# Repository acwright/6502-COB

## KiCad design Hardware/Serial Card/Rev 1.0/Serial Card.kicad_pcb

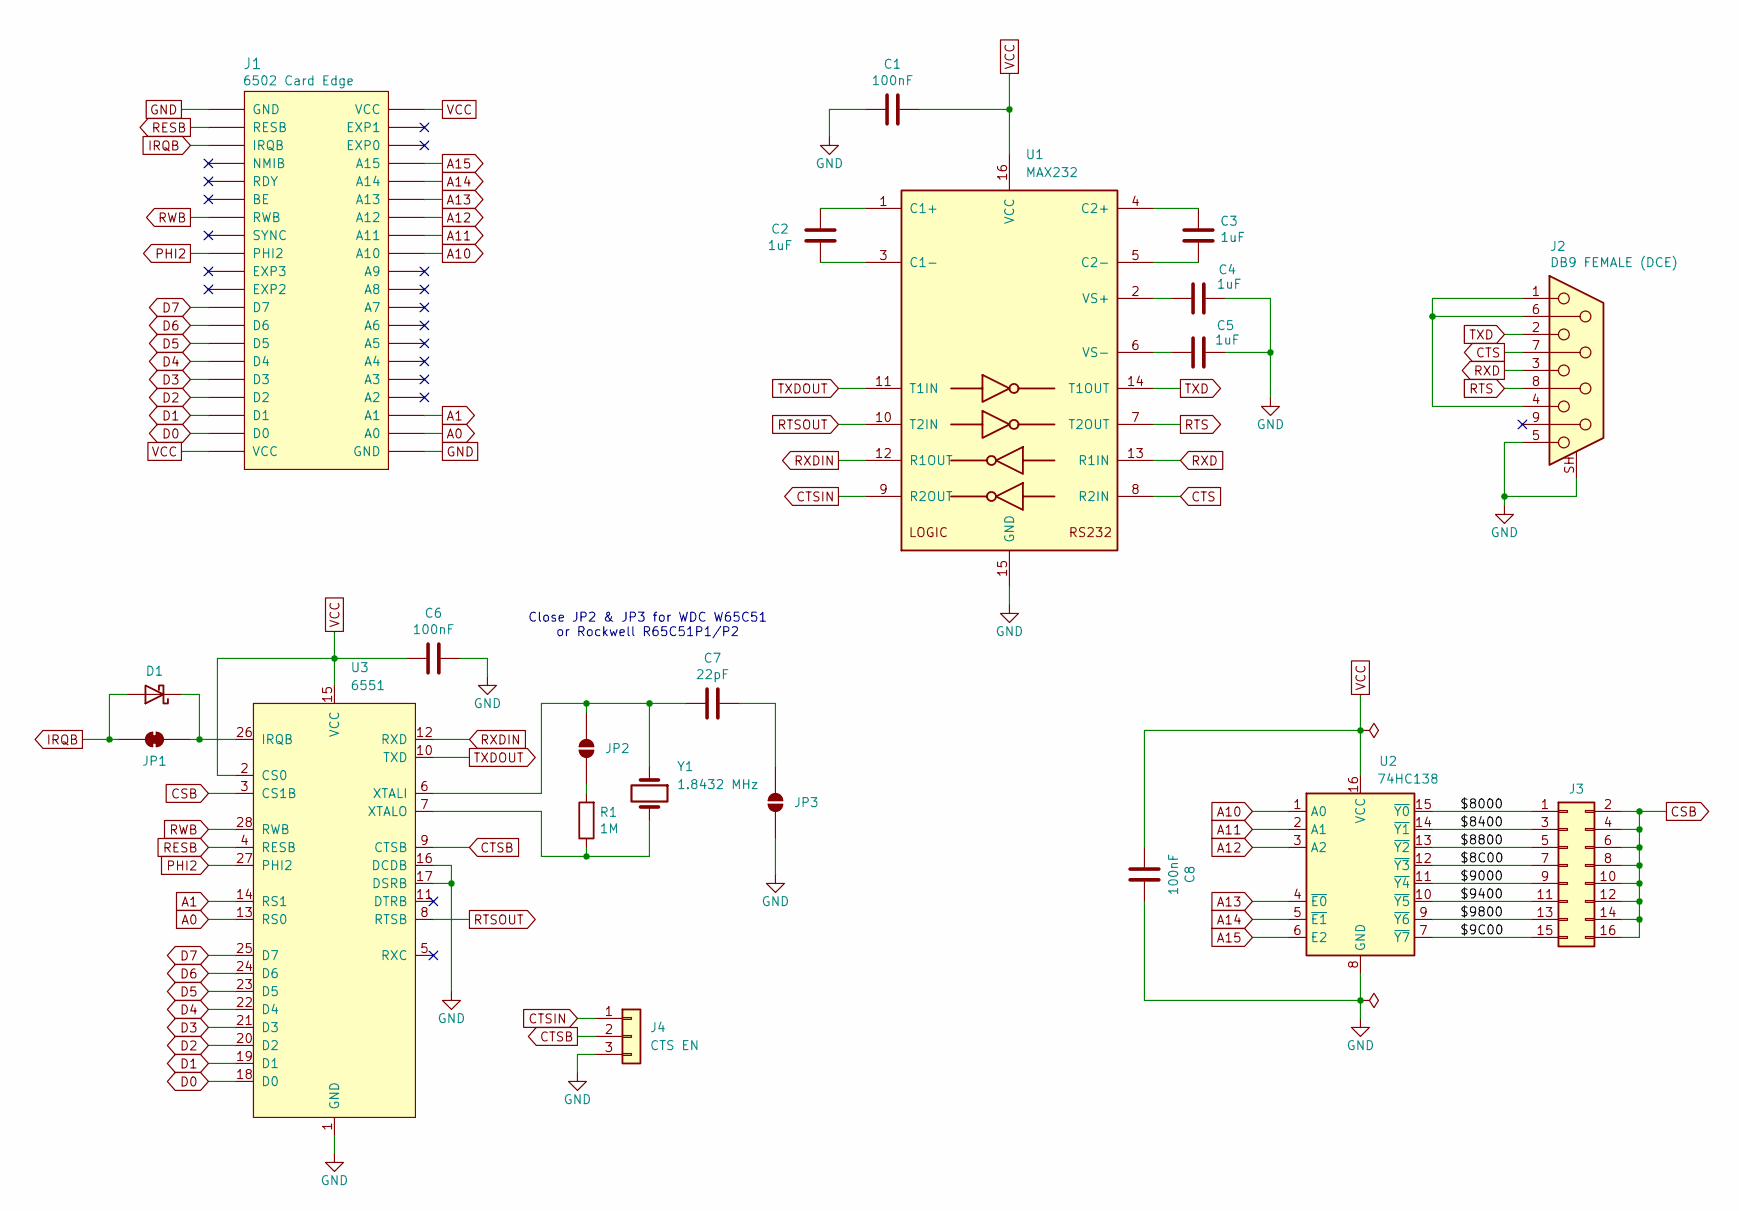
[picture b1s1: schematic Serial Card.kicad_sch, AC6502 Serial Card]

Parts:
C1, C6, C8: 100nF; C_0805_2012Metric; LCSC C49678
C2, C3, C4, C5: 1uF; C_0805_2012Metric; LCSC C28323
C7: 22pF; C_0805_2012Metric; LCSC C1804
D1: BAT85; D_DO-35_SOD27_P7.62mm_Horizontal; Digikey BAT85SCT-ND
J1: 6502 Card Edge
J2: DB9 FEMALE (DCE); DSUB-9_Socket_Horizontal_P2.77x2.84mm_EdgePinOffset7.70mm_H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; Digikey 609-1487-ND
J3: Conn_02x08_Odd_Even; PinHeader_2x08_P2.54mm_Vertical; Digikey S2011EC-40-ND
J4: CTS EN; PinHeader_1x03_P2.54mm_Vertical; Digikey S1011EC-40-ND
JP1: SolderJumper_2_Bridged; SolderJumper-2_P1.3mm_Bridged_RoundedPad1.0x1.5mm
JP2, JP3: SolderJumper_2_Open; SolderJumper-2_P1.3mm_Open_RoundedPad1.0x1.5mm
R1: 1M; R_0805_2012Metric; LCSC C17514
U1: MAX232; SOIC-16; LCSC C59824
U2: 74HC138; SOIC-16_3.9x9.9mm_P1.27mm; LCSC C5602
U3: 6551; DIP-28_W15.24mm_Socket_LongPads
Y1: 1.8432 MHz; Crystal_HC49-U_Vertical; Digikey 535-9009-ND

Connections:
/$8C00: J3.7, U2.12 (~Y3)
/$9C00: J3.15, U2.7 (~Y7)
/$8000: J3.1, U2.15 (~Y0)
/$8400: J3.3, U2.14 (~Y1)
/$8800: J3.5, U2.13 (~Y2)
/$9000: J3.9, U2.11 (~Y4)
/$9400: J3.11, U2.10 (~Y5)
/$9800: J3.13, U2.9 (~Y6)
A0: J1.A0, U3.13 (RS0)
A1: J1.A1, U3.14 (RS1)
A10: J1.A10, U2.1 (A0)
A11: J1.A11, U2.2 (A1)
A12: J1.A12, U2.3 (A2)
A13: J1.A13, U2.4 (~E0)
A14: J1.A14, U2.5 (~E1)
A15: J1.A15, U2.6 (E2)
CSB: J3.2, J3.4, J3.6, J3.8, J3.10, J3.12, J3.14, J3.16, U3.3 (CS1B)
CTS: J2.7, U1.8 (R2IN)
CTSB: J4.2, U3.9 (CTSB)
CTSIN: J4.1, U1.9 (R2OUT)
D0: J1.D0, U3.18 (D0)
D1: J1.D1, U3.19 (D1)
D2: J1.D2, U3.20 (D2)
D3: J1.D3, U3.21 (D3)
D4: J1.D4, U3.22 (D4)
D5: J1.D5, U3.23 (D5)
D6: J1.D6, U3.24 (D6)
D7: J1.D7, U3.25 (D7)
GND: C1.1, C4.2, C5.2, C6.2, C8.2, J1.GND, J2.5, J2.SH (PAD), J4.3, JP3.1 (A), U1.15 (GND), U2.8 (GND), U3.1 (GND), U3.16 (DCDB), U3.17 (DSRB)
IRQB: D1.2 (A), J1.IRQB, JP1.1 (A)
unnamed: D1.1 (K), JP1.2 (B), U3.26 (IRQB)
unnamed: J2.1, J2.4, J2.6
unnamed: JP2.1 (A), R1.2
unnamed: C7.2, JP2.2 (B), U3.6 (XTALI), Y1.1
unnamed: C7.1, JP3.2 (B)
unnamed: C2.1, U1.1 (C1+)
unnamed: C2.2, U1.3 (C1-)
unnamed: C3.1, U1.4 (C2+)
unnamed: C3.2, U1.5 (C2-)
unnamed: C4.1, U1.2 (VS+)
unnamed: C5.1, U1.6 (VS-)
unnamed: R1.1, U3.7 (XTALO), Y1.2
PHI2: J1.PHI2, U3.27 (PHI2)
RESB: J1.RESB, U3.4 (RESB)
RTS: J2.8, U1.7 (T2OUT)
RTSOUT: U1.10 (T2IN), U3.8 (RTSB)
RWB: J1.RWB, U3.28 (RWB)
RXD: J2.3, U1.13 (R1IN)
RXDIN: U1.12 (R1OUT), U3.12 (RXD)
TXD: J2.2, U1.14 (T1OUT)
TXDOUT: U1.11 (T1IN), U3.10 (TXD)
VCC: C1.2, C6.1, C8.1, J1.VCC, U1.16 (VCC), U2.16 (VCC), U3.2 (CS0), U3.15 (VCC)

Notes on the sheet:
Close JP2 & JP3 for WDC W65C51 or Rockwell R65C51P1/P2

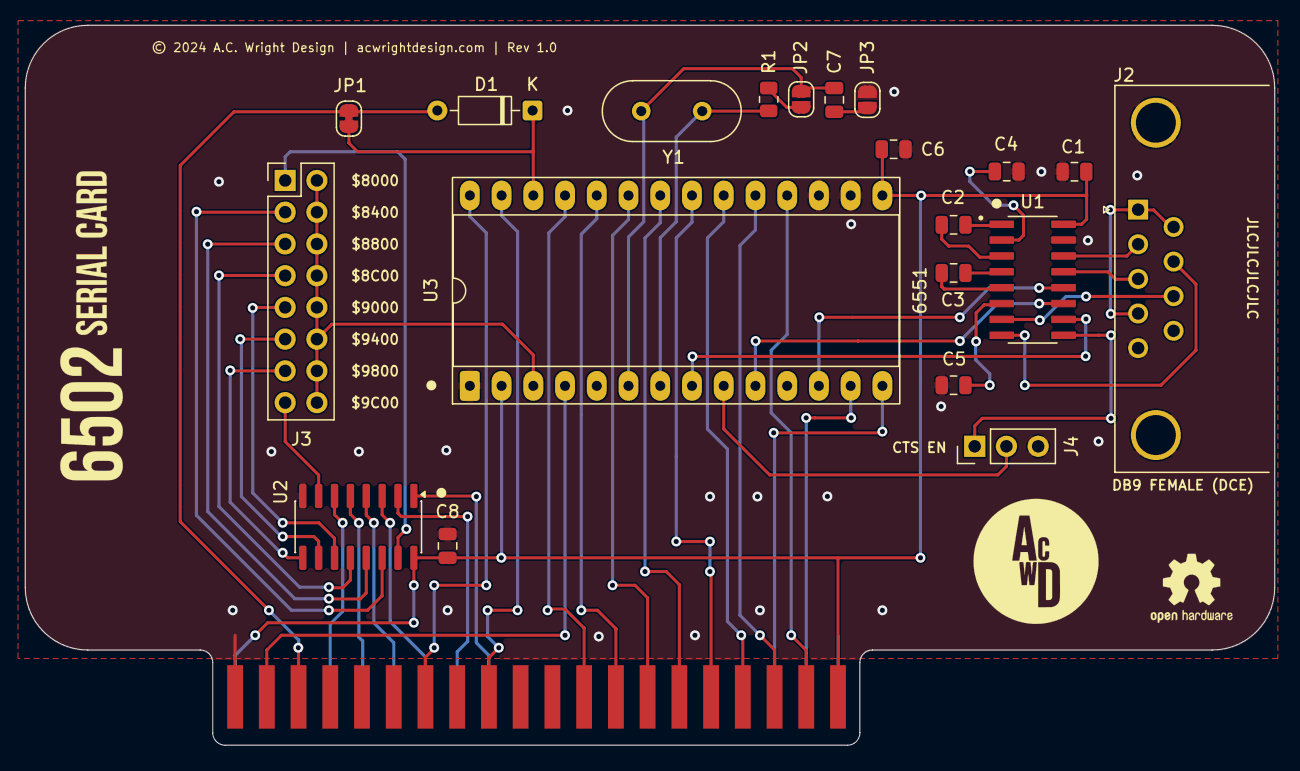
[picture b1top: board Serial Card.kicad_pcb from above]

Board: 2 copper layers, 100.0 x 57.6 mm, 21 parts (0 on the bottom side), 52 nets.

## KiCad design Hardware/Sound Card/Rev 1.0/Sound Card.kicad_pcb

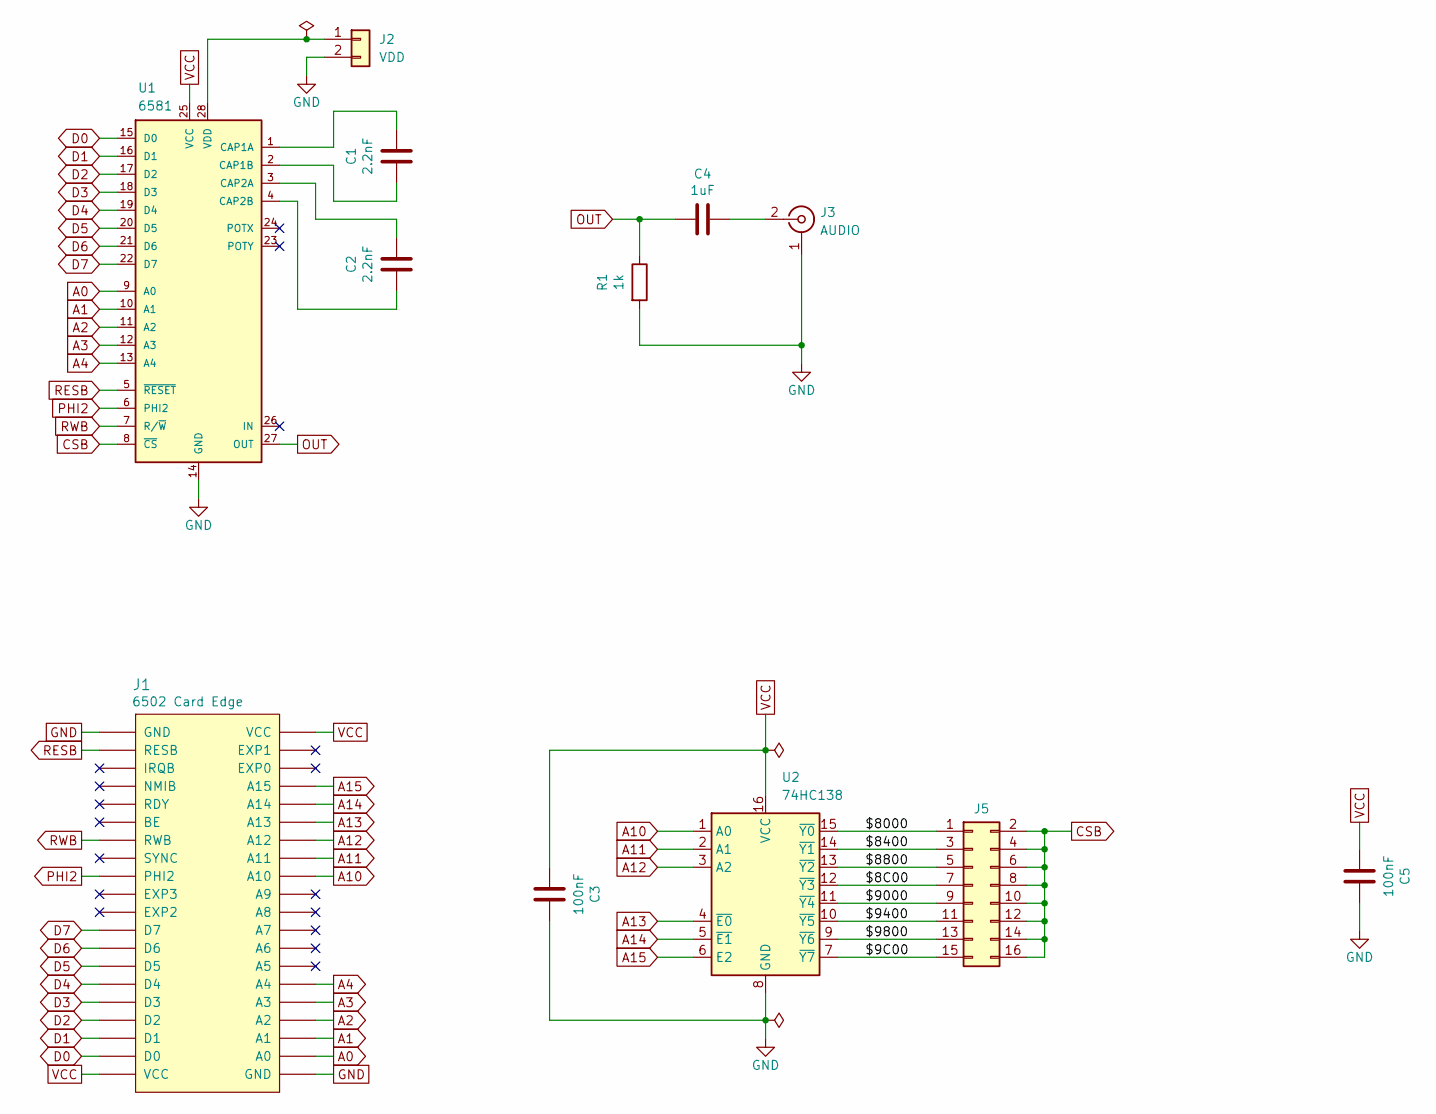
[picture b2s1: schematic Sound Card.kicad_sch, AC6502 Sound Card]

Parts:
C1, C2: 2.2nF; C_0805_2012Metric; LCSC C28260
C3, C5: 100nF; C_0805_2012Metric; LCSC C49678
C4: 1uF; C_0805_2012Metric; LCSC C28323
J1: 6502 Card Edge
J2: VDD; JST_XH_B2B-XH-A_1x02_P2.50mm_Vertical; Digikey 455-B2B-XH-A-ND
J3: AUDIO; RCA Jack White; Digikey PJRAN1X1U02X-ND
J5: Conn_02x08_Odd_Even; PinHeader_2x08_P2.54mm_Vertical; Digikey S2011EC-40-ND
R1: 1k; R_0805_2012Metric; LCSC C17513
U1: 6581; DIP-28_W15.24mm_Socket_LongPads
U2: 74HC138; SOIC-16_3.9x9.9mm_P1.27mm; LCSC C5602

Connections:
/$8C00: J5.7, U2.12 (~Y3)
/$9C00: J5.15, U2.7 (~Y7)
/$8000: J5.1, U2.15 (~Y0)
/$8400: J5.3, U2.14 (~Y1)
/$8800: J5.5, U2.13 (~Y2)
/$9000: J5.9, U2.11 (~Y4)
/$9400: J5.11, U2.10 (~Y5)
/$9800: J5.13, U2.9 (~Y6)
A0: J1.A0, U1.9 (A0)
A1: J1.A1, U1.10 (A1)
A2: J1.A2, U1.11 (A2)
A3: J1.A3, U1.12 (A3)
A4: J1.A4, U1.13 (A4)
A10: J1.A10, U2.1 (A0)
A11: J1.A11, U2.2 (A1)
A12: J1.A12, U2.3 (A2)
A13: J1.A13, U2.4 (~E0)
A14: J1.A14, U2.5 (~E1)
A15: J1.A15, U2.6 (E2)
CSB: J5.2, J5.4, J5.6, J5.8, J5.10, J5.12, J5.14, J5.16, U1.8 (~CS)
D0: J1.D0, U1.15 (D0)
D1: J1.D1, U1.16 (D1)
D2: J1.D2, U1.17 (D2)
D3: J1.D3, U1.18 (D3)
D4: J1.D4, U1.19 (D4)
D5: J1.D5, U1.20 (D5)
D6: J1.D6, U1.21 (D6)
D7: J1.D7, U1.22 (D7)
GND: C3.2, C5.2, J1.GND, J2.2, J3.1 (Ext), R1.2, U1.14 (GND), U2.8 (GND)
unnamed: J2.1, U1.28 (VDD)
unnamed: C4.2, J3.2 (In)
unnamed: C1.2, U1.1 (CAP1A)
unnamed: C1.1, U1.2 (CAP1B)
unnamed: C2.2, U1.3 (CAP2A)
unnamed: C2.1, U1.4 (CAP2B)
OUT: C4.1, R1.1, U1.27 (OUT)
PHI2: J1.PHI2, U1.6 (PHI2)
RESB: J1.RESB, U1.5 (~RESET)
RWB: J1.RWB, U1.7 (R/~W)
VCC: C3.1, C5.1, J1.VCC, U1.25 (VCC), U2.16 (VCC)

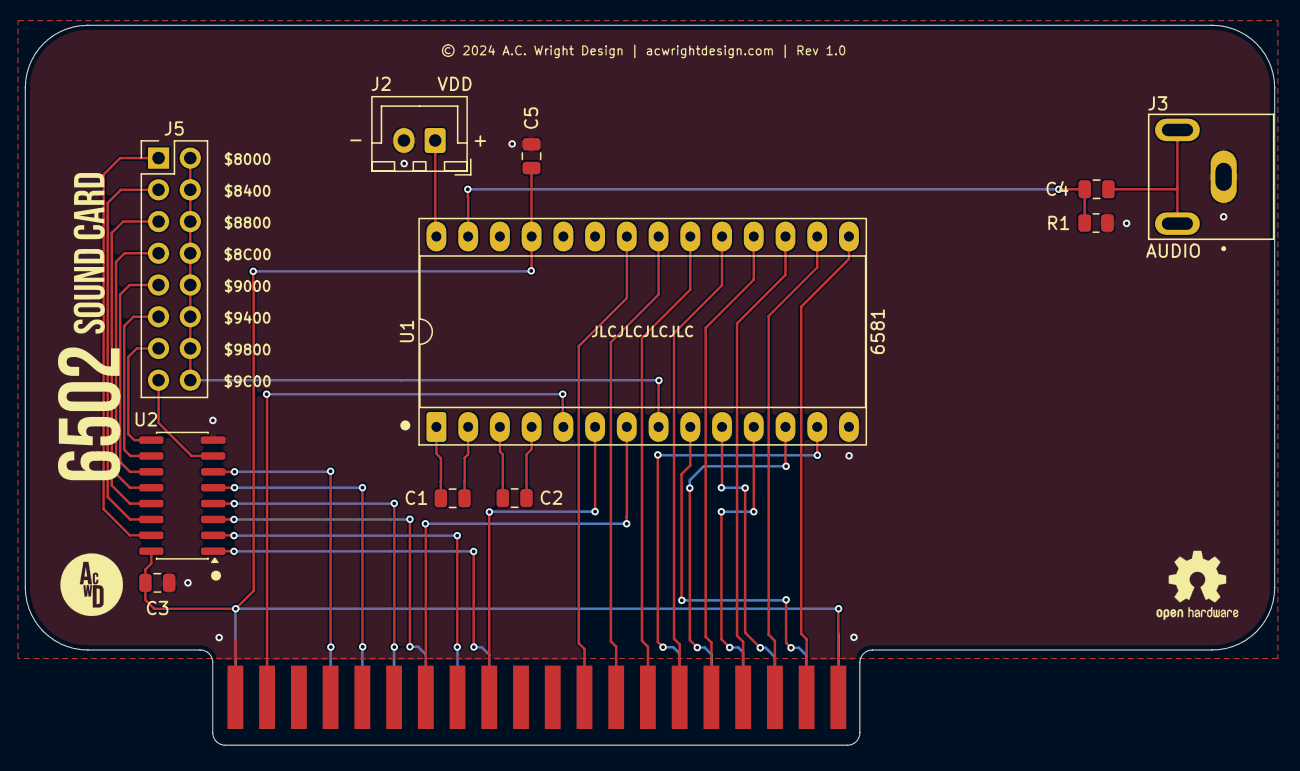
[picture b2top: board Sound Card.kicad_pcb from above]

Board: 2 copper layers, 100.0 x 57.6 mm, 12 parts (0 on the bottom side), 40 nets.

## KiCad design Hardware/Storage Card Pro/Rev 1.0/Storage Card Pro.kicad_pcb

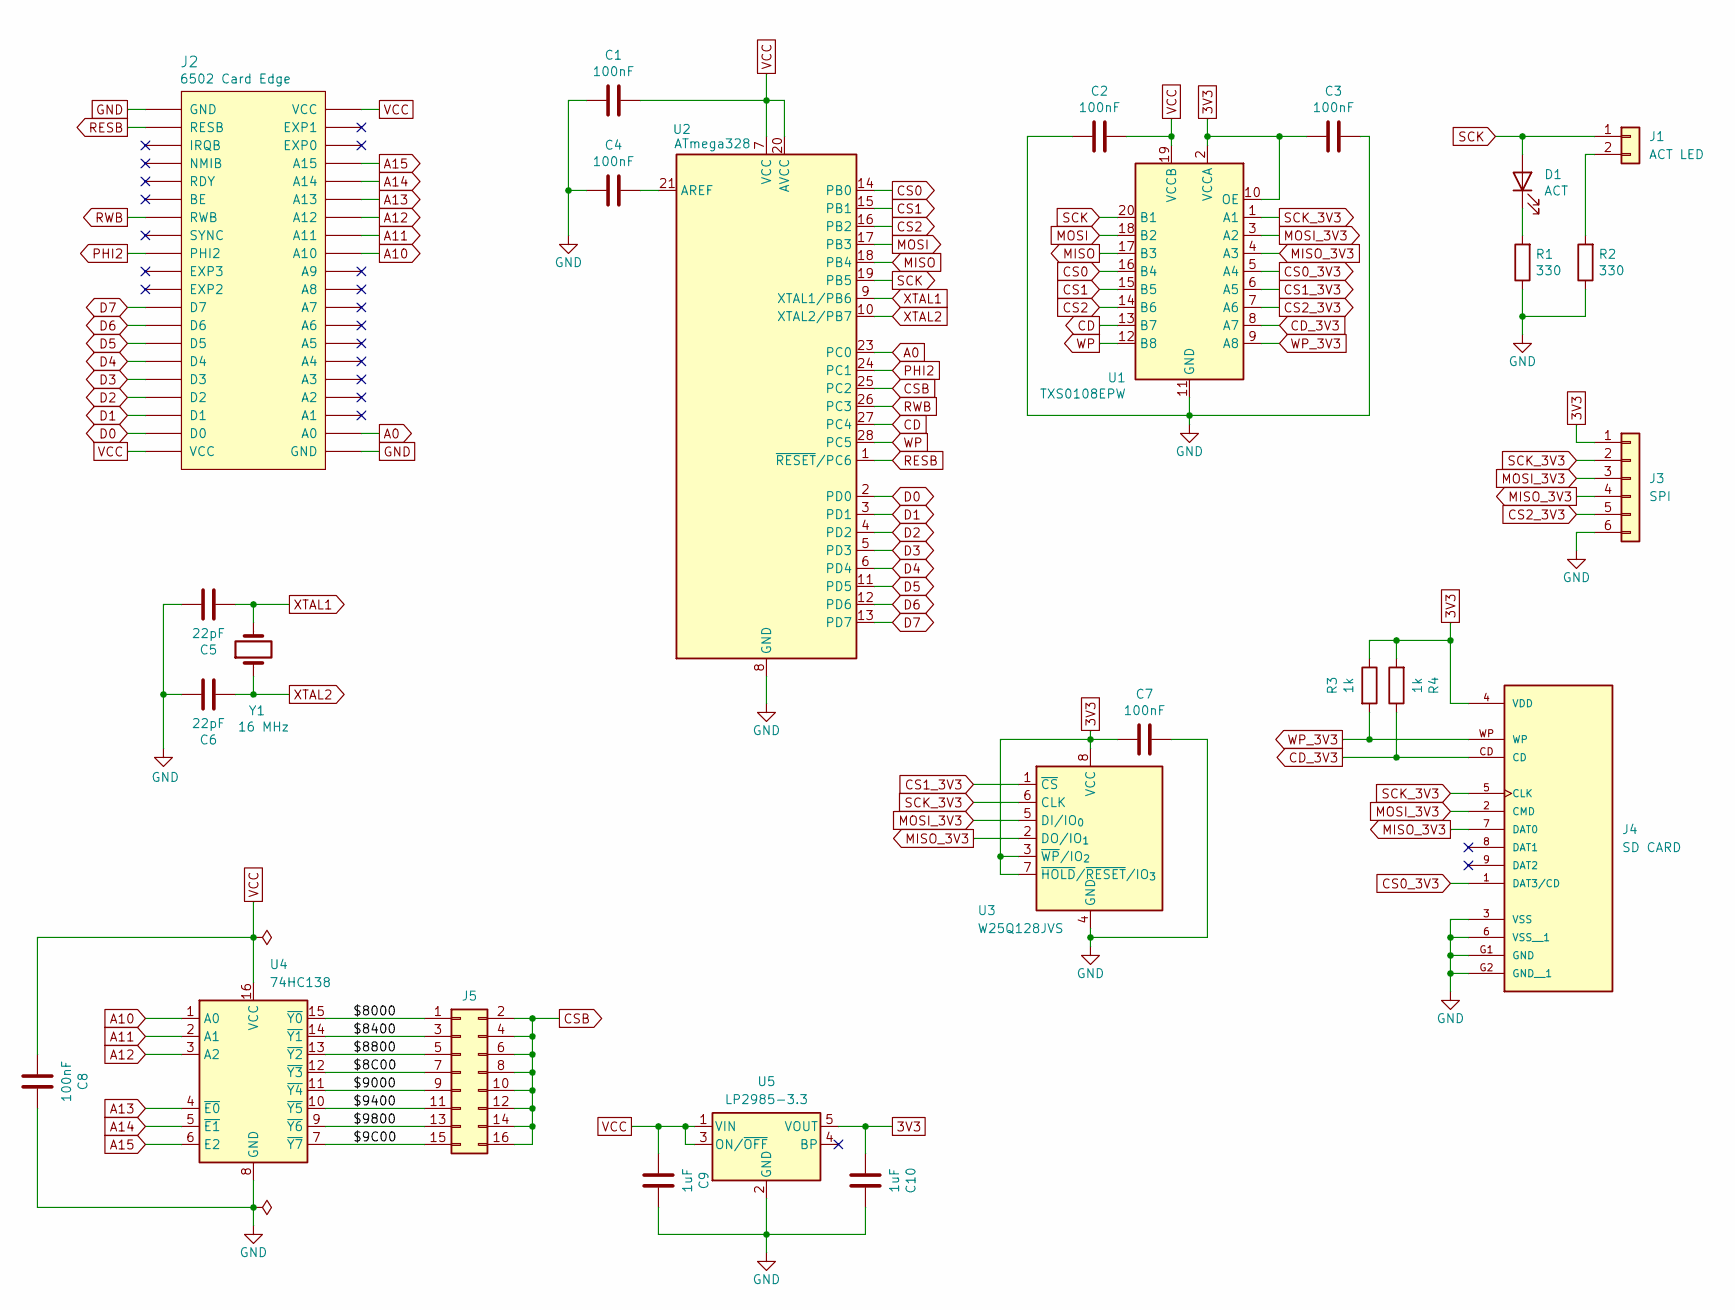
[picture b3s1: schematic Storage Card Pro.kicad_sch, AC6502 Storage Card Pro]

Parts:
C1, C2, C3, C4, C7, C8: 100nF; C_0805_2012Metric; LCSC C49678
C5, C6: 22pF; C_Disc_D5.0mm_W2.5mm_P2.50mm; Digikey 478-4846-ND
C9, C10: 1uF; C_0805_2012Metric; LCSC C28323
D1: ACT; LED_0805_2012Metric; LCSC C2297
J1: ACT LED; JST_XH_B2B-XH-A_1x02_P2.50mm_Vertical; Digikey 455-B2B-XH-A-ND
J2: 6502 Card Edge
J3: SPI; PinHeader_1x06_P2.54mm_Horizontal; Digikey 2057-PH1RB-06-UA-ND
J4: SD CARD; SD Card Socket; LCSC C569097
J5: Conn_02x08_Odd_Even; PinHeader_2x08_P2.54mm_Vertical; Digikey S2011EC-40-ND
R1, R2: 330; R_0805_2012Metric; LCSC C17630
R3, R4: 1k; R_0805_2012Metric; LCSC C17513
U1: TXS0108EPW; TSSOP-20_4.4x6.5mm_P0.65mm; LCSC C17206
U2: ATmega328; DIP-28_W7.62mm_Socket_LongPads; Digikey ATMEGA328P-PU-ND
U3: W25Q128JVS; SOIC-8_5.3x5.3mm_P1.27mm; LCSC C97521
U4: 74HC138; SOIC-16_3.9x9.9mm_P1.27mm; LCSC C5602
U5: LP2985-3.3; SOT-23-5; LCSC C95414
Y1: 16 MHz; Crystal_HC49-U_Vertical; Digikey X1103-ND

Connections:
3V3: C3.1, C7.1, C10.1, J3.1, J4.4 (VDD), R3.1, R4.2, U1.2 (VCCA), U1.10 (OE), U3.3 (~WP/IO_{2}), U3.7 (~HOLD/~RESET/IO_{3}), U3.8 (VCC), U5.5 (VOUT)
/$8C00: J5.7, U4.12 (~Y3)
/$9C00: J5.15, U4.7 (~Y7)
/$8000: J5.1, U4.15 (~Y0)
/$8400: J5.3, U4.14 (~Y1)
/$8800: J5.5, U4.13 (~Y2)
/$9000: J5.9, U4.11 (~Y4)
/$9400: J5.11, U4.10 (~Y5)
/$9800: J5.13, U4.9 (~Y6)
A0: J2.A0, U2.23 (PC0)
A10: J2.A10, U4.1 (A0)
A11: J2.A11, U4.2 (A1)
A12: J2.A12, U4.3 (A2)
A13: J2.A13, U4.4 (~E0)
A14: J2.A14, U4.5 (~E1)
A15: J2.A15, U4.6 (E2)
CD: U1.13 (B7), U2.27 (PC4)
CD_3V3: J4.CD, R4.1, U1.8 (A7)
CS0: U1.16 (B4), U2.14 (PB0)
CS0_3V3: J4.1 (DAT3/CD), U1.5 (A4)
CS1: U1.15 (B5), U2.15 (PB1)
CS1_3V3: U1.6 (A5), U3.1 (~CS)
CS2: U1.14 (B6), U2.16 (PB2)
CS2_3V3: J3.5, U1.7 (A6)
CSB: J5.2, J5.4, J5.6, J5.8, J5.10, J5.12, J5.14, J5.16, U2.25 (PC2)
D0: J2.D0, U2.2 (PD0)
D1: J2.D1, U2.3 (PD1)
D2: J2.D2, U2.4 (PD2)
D3: J2.D3, U2.5 (PD3)
D4: J2.D4, U2.6 (PD4)
D5: J2.D5, U2.11 (PD5)
D6: J2.D6, U2.12 (PD6)
D7: J2.D7, U2.13 (PD7)
GND: C1.1, C2.1, C3.2, C4.1, C5.2, C6.2, C7.2, C8.2, C9.2, C10.2, J2.GND, J3.6, J4.3 (VSS), J4.6 (VSS__1), J4.G1 (GND), J4.G2 (GND__1), R1.1, R2.1, U1.11 (GND), U2.8 (GND), U2.22 (GND), U3.4 (GND), U4.8 (GND), U5.2 (GND)
MISO: U1.17 (B3), U2.18 (PB4)
MISO_3V3: J3.4, J4.7 (DAT0), U1.4 (A3), U3.2 (DO/IO_{1})
MOSI: U1.18 (B2), U2.17 (PB3)
MOSI_3V3: J3.3, J4.2 (CMD), U1.3 (A2), U3.5 (DI/IO_{0})
unnamed: D1.1 (K), R1.2
unnamed: J1.2, R2.2
unnamed: C4.2, U2.21 (AREF)
PHI2: J2.PHI2, U2.24 (PC1)
RESB: J2.RESB, U2.1 (~RESET/PC6)
RWB: J2.RWB, U2.26 (PC3)
SCK: D1.2 (A), J1.1, U1.20 (B1), U2.19 (PB5)
SCK_3V3: J3.2, J4.5 (CLK), U1.1 (A1), U3.6 (CLK)
VCC: C1.2, C2.2, C8.1, C9.1, J2.VCC, U1.19 (VCCB), U2.7 (VCC), U2.20 (AVCC), U4.16 (VCC), U5.1 (VIN), U5.3 (ON/~OFF)
WP: U1.12 (B8), U2.28 (PC5)
WP_3V3: J4.WP, R3.2, U1.9 (A8)
XTAL1: C5.1, U2.9 (XTAL1/PB6), Y1.2
XTAL2: C6.1, U2.10 (XTAL2/PB7), Y1.1

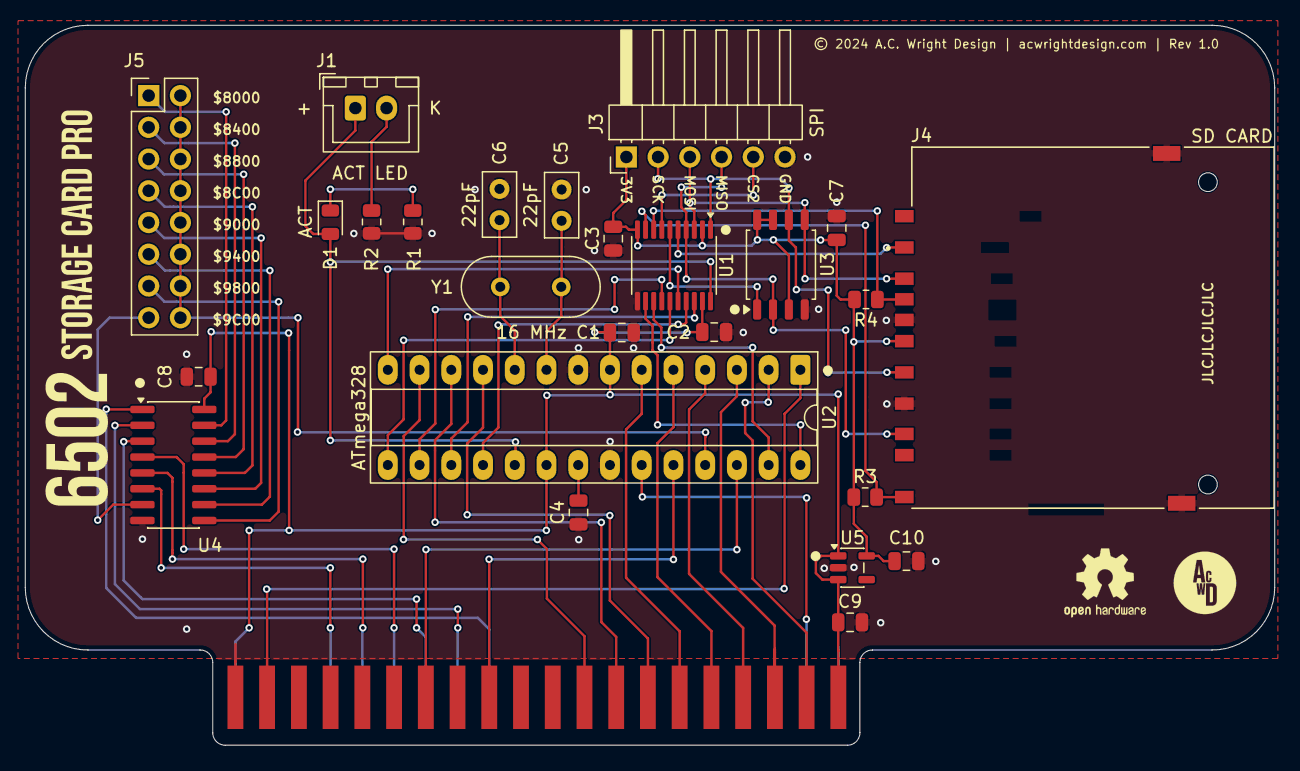
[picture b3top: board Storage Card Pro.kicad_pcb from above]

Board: 2 copper layers, 100.0 x 57.6 mm, 26 parts (0 on the bottom side), 51 nets.

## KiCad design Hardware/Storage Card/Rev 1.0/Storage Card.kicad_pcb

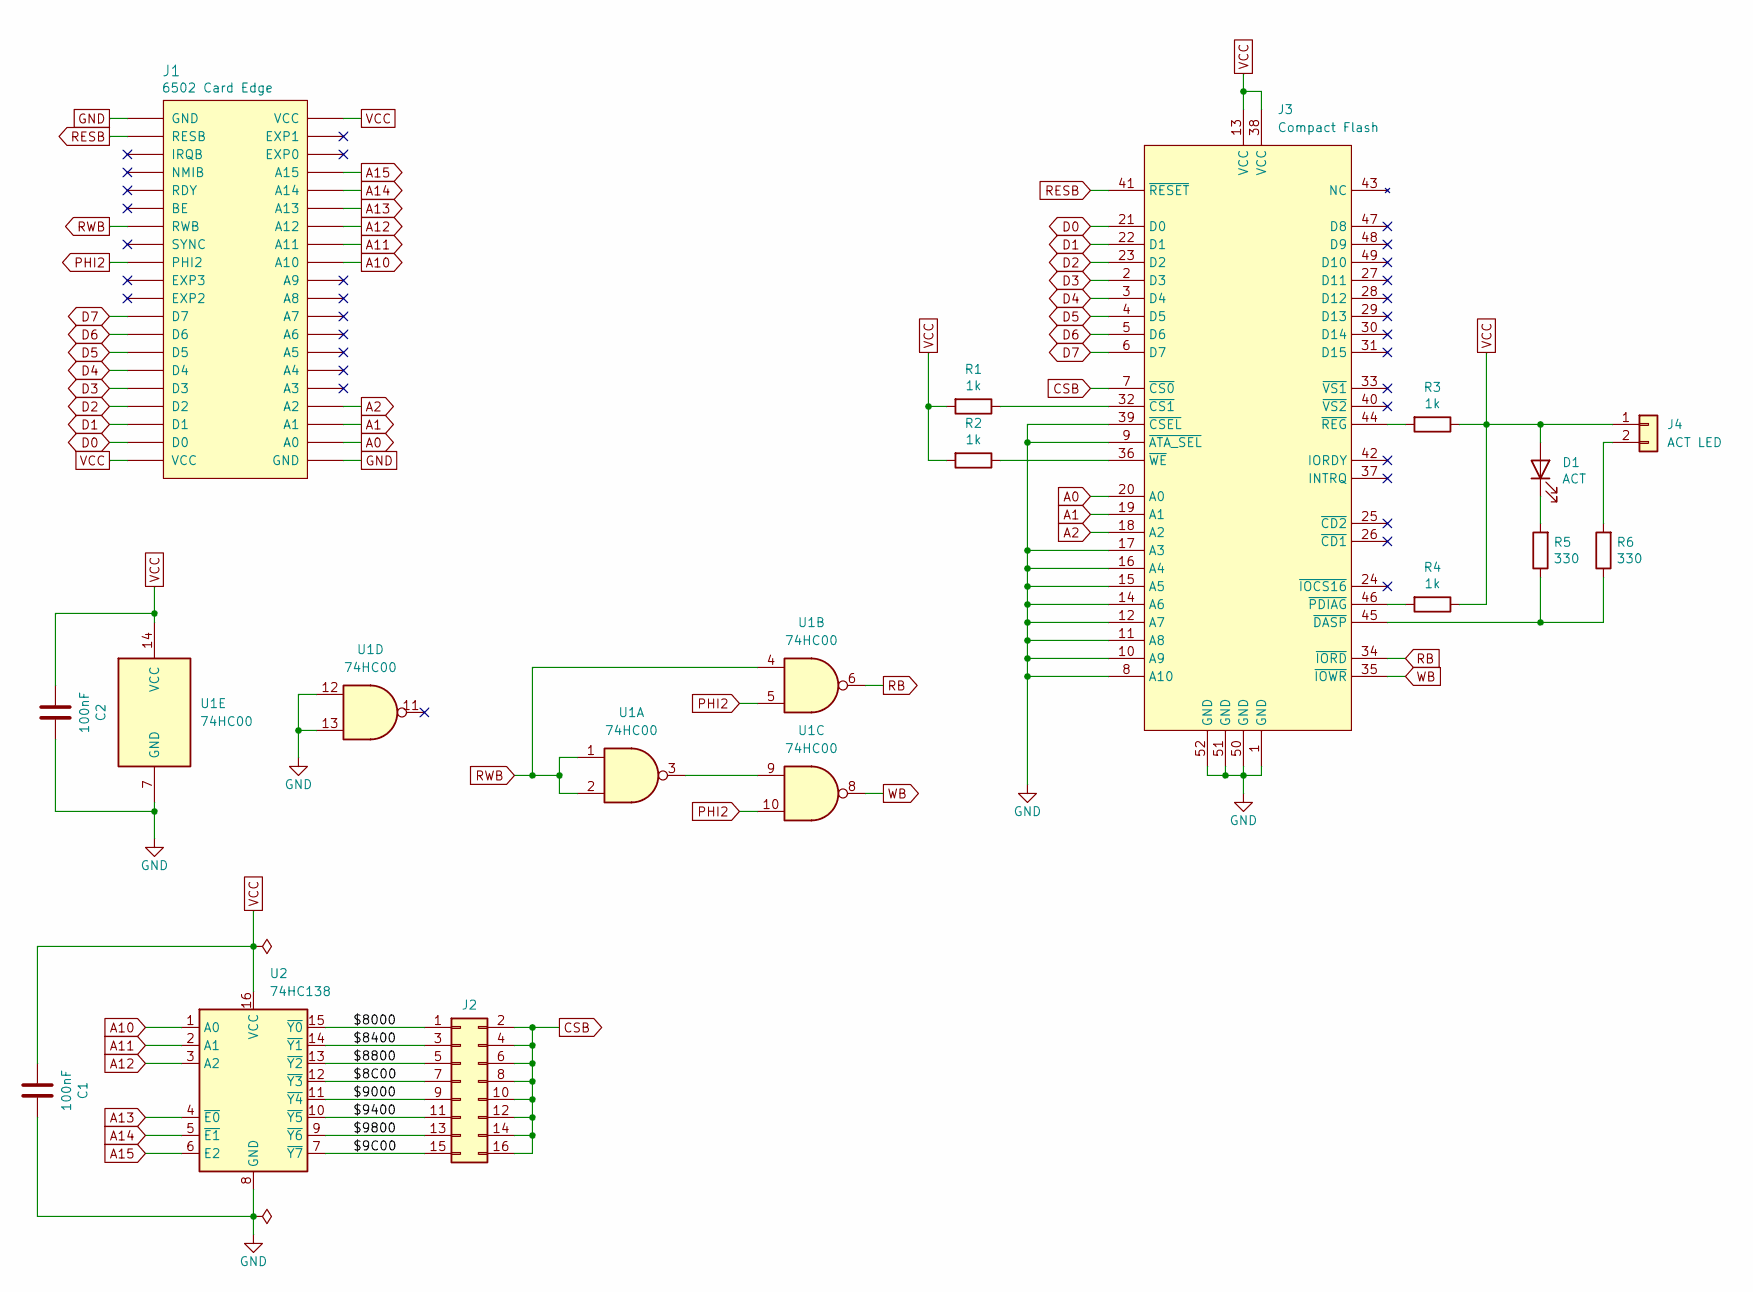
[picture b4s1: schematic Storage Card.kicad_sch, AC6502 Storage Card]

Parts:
C1, C2: 100nF; C_0805_2012Metric; LCSC C49678
D1: ACT; LED_0805_2012Metric; LCSC C2297
J1: 6502 Card Edge
J2: Conn_02x08_Odd_Even; PinHeader_2x08_P2.54mm_Vertical; Digikey S2011EC-40-ND
J3: Compact Flash; CompactFlash Socket Plated Pegs; LCSC C444350
J4: ACT LED; JST_XH_B2B-XH-A_1x02_P2.50mm_Vertical; Digikey 455-B2B-XH-A-ND
R1, R2, R3, R4: 1k; R_0805_2012Metric; LCSC C17513
R5, R6: 330; R_0805_2012Metric; LCSC C17630
U1: 74HC00; SOIC-14_3.9x8.7mm_P1.27mm; LCSC C5586
U2: 74HC138; SOIC-16_3.9x9.9mm_P1.27mm; LCSC C5602

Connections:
/$8C00: J2.7, U2.12 (~Y3)
/$9C00: J2.15, U2.7 (~Y7)
/$8000: J2.1, U2.15 (~Y0)
/$8400: J2.3, U2.14 (~Y1)
/$8800: J2.5, U2.13 (~Y2)
/$9000: J2.9, U2.11 (~Y4)
/$9400: J2.11, U2.10 (~Y5)
/$9800: J2.13, U2.9 (~Y6)
A0: J1.A0, J3.20 (A0)
A1: J1.A1, J3.19 (A1)
A2: J1.A2, J3.18 (A2)
A10: J1.A10, U2.1 (A0)
A11: J1.A11, U2.2 (A1)
A12: J1.A12, U2.3 (A2)
A13: J1.A13, U2.4 (~E0)
A14: J1.A14, U2.5 (~E1)
A15: J1.A15, U2.6 (E2)
CSB: J2.2, J2.4, J2.6, J2.8, J2.10, J2.12, J2.14, J2.16, J3.7 (~CS0)
D0: J1.D0, J3.21 (D0)
D1: J1.D1, J3.22 (D1)
D2: J1.D2, J3.23 (D2)
D3: J1.D3, J3.2 (D3)
D4: J1.D4, J3.3 (D4)
D5: J1.D5, J3.4 (D5)
D6: J1.D6, J3.5 (D6)
D7: J1.D7, J3.6 (D7)
GND: C1.2, C2.2, J1.GND, J3.1 (GND), J3.8 (A10), J3.9 (~ATA_SEL), J3.10 (A9), J3.11 (A8), J3.12 (A7), J3.14 (A6), J3.15 (A5), J3.16 (A4), J3.17 (A3), J3.39 (~CSEL), J3.50 (GND), J3.51 (GND), J3.52 (GND), U1.7 (GND), U1.12, U1.13, U2.8 (GND)
unnamed: D1.1 (K), R5.2
unnamed: J3.32 (~CS1), R1.1
unnamed: J3.45 (~DASP), R5.1, R6.1
unnamed: J3.46 (~PDIAG), R4.2
unnamed: J3.44 (~REG), R3.2
unnamed: J3.36 (~WE), R2.1
unnamed: J4.2, R6.2
unnamed: U1.3, U1.9
PHI2: J1.PHI2, U1.5, U1.10
RB: J3.34 (~IORD), U1.6
RESB: J1.RESB, J3.41 (~RESET)
RWB: J1.RWB, U1.1, U1.2, U1.4
VCC: C1.1, C2.1, D1.2 (A), J1.VCC, J3.13 (VCC), J3.38 (VCC), J4.1, R1.2, R2.2, R3.1, R4.1, U1.14 (VCC), U2.16 (VCC)
WB: J3.35 (~IOWR), U1.8

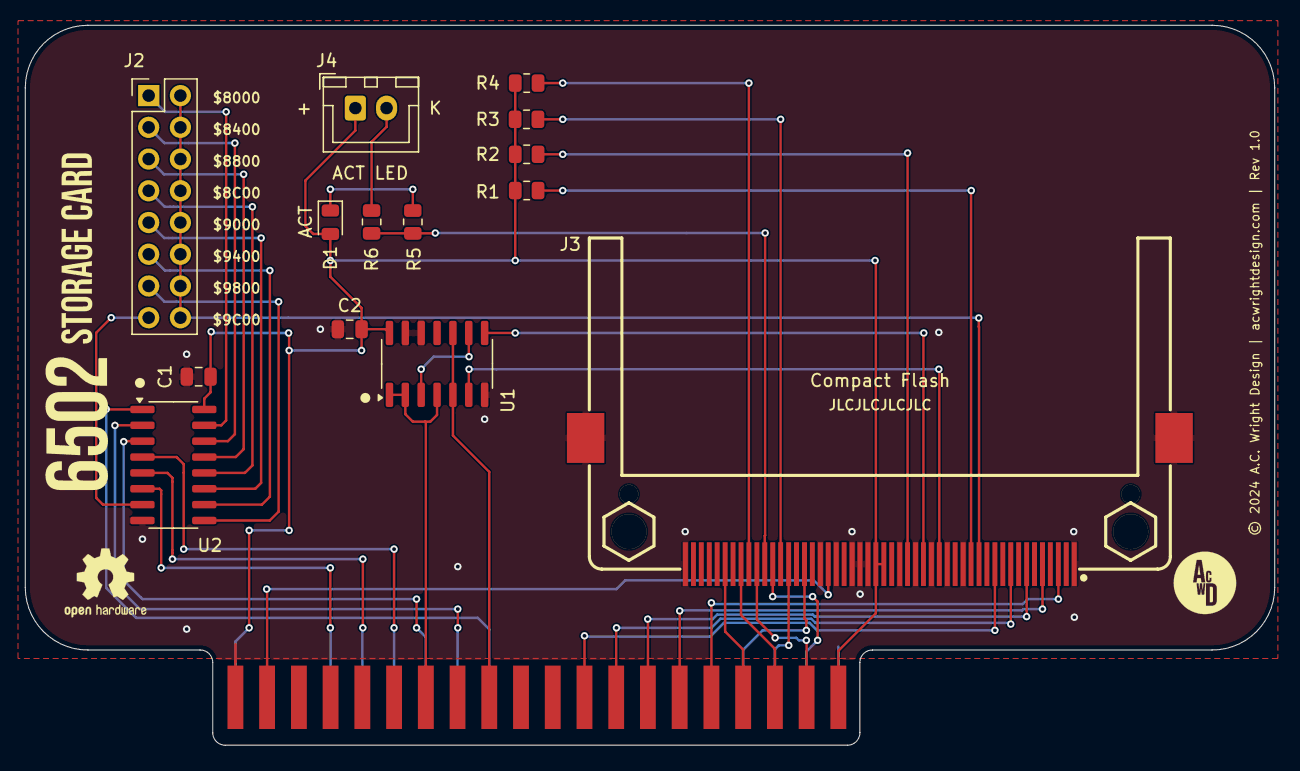
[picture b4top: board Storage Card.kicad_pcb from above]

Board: 2 copper layers, 100.0 x 57.6 mm, 15 parts (0 on the bottom side), 41 nets.

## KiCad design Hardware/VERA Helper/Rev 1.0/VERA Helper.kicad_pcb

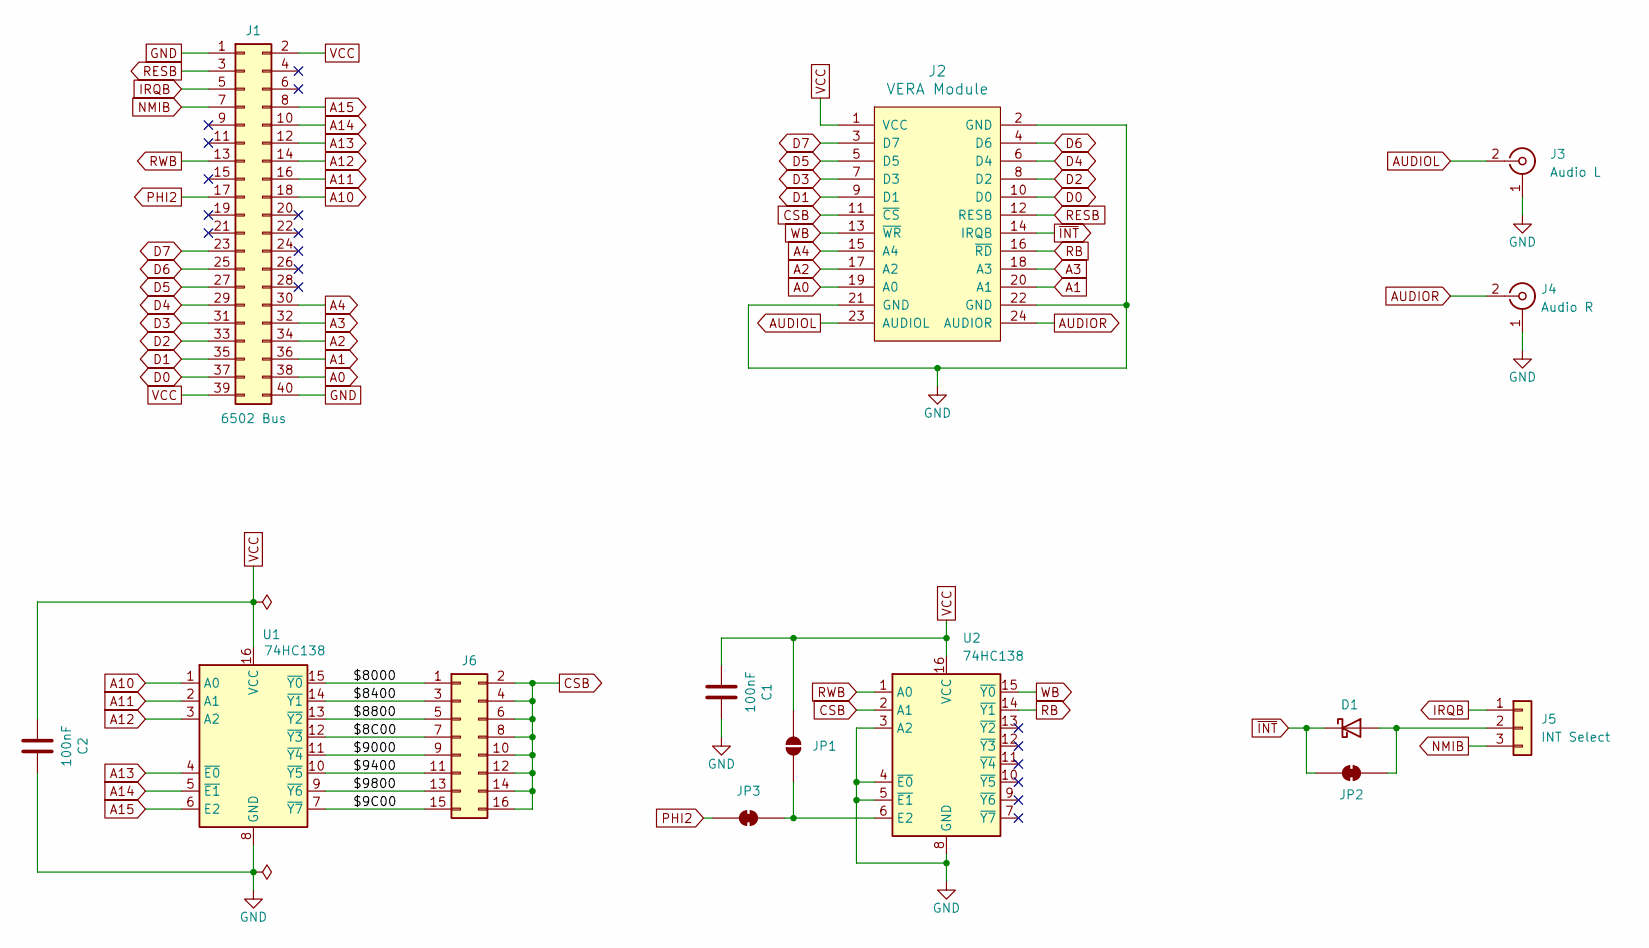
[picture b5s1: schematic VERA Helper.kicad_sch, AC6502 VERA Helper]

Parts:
C1, C2: 100nF; C_Disc_D5.0mm_W2.5mm_P5.00mm; Digikey 478-3188-ND
D1: BAT85; D_DO-35_SOD27_P7.62mm_Horizontal; Digikey BAT85SCT-ND
J1: 6502 Bus; 6502 Bus Connector; Digikey 732-5401-ND
J2: VERA Module; PinHeader_2x12_P2.54mm_Vertical; Digikey S2011EC-40-ND
J3: Audio L; RCA Jack White; Digikey PJRAN1X1U02X-ND
J4: Audio R; RCA Jack White; Digikey PJRAN1X1U03X-ND
J5: INT Select; PinHeader_1x03_P2.54mm_Vertical; Digikey S1011EC-40-ND
J6: Conn_02x08_Odd_Even; PinHeader_2x08_P2.54mm_Vertical; Digikey S2011EC-40-ND
JP1: SolderJumper_2_Open; SolderJumper-2_P1.3mm_Open_RoundedPad1.0x1.5mm
JP2, JP3: SolderJumper_2_Bridged; SolderJumper-2_P1.3mm_Bridged_RoundedPad1.0x1.5mm
U1, U2: 74HC138; DIP-16_W7.62mm_Socket_LongPads; Digikey 296-1575-5-ND

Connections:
/$8C00: J6.7, U1.12 (~Y3)
/$9C00: J6.15, U1.7 (~Y7)
/$8000: J6.1, U1.15 (~Y0)
/$8400: J6.3, U1.14 (~Y1)
/$8800: J6.5, U1.13 (~Y2)
/$9000: J6.9, U1.11 (~Y4)
/$9400: J6.11, U1.10 (~Y5)
/$9800: J6.13, U1.9 (~Y6)
A0: J1.38, J2.19 (A0)
A1: J1.36, J2.20 (A1)
A2: J1.34, J2.17 (A2)
A3: J1.32, J2.18 (A3)
A4: J1.30, J2.15 (A4)
A10: J1.18, U1.1 (A0)
A11: J1.16, U1.2 (A1)
A12: J1.14, U1.3 (A2)
A13: J1.12, U1.4 (~E0)
A14: J1.10, U1.5 (~E1)
A15: J1.8, U1.6 (E2)
AUDIOL: J2.23 (AUDIOL), J3.2 (In)
AUDIOR: J2.24 (AUDIOR), J4.2 (In)
CSB: J2.11 (~CS), J6.2, J6.4, J6.6, J6.8, J6.10, J6.12, J6.14, J6.16, U2.2 (A1)
D0: J1.37, J2.10 (D0)
D1: J1.35, J2.9 (D1)
D2: J1.33, J2.8 (D2)
D3: J1.31, J2.7 (D3)
D4: J1.29, J2.6 (D4)
D5: J1.27, J2.5 (D5)
D6: J1.25, J2.4 (D6)
D7: J1.23, J2.3 (D7)
GND: C1.2, C2.2, J1.1, J1.40, J2.2 (GND), J2.21 (GND), J2.22 (GND), J3.1 (Ext), J4.1 (Ext), U1.8 (GND), U2.3 (A2), U2.4 (~E0), U2.5 (~E1), U2.8 (GND)
IRQB: J1.5, J5.1
NMIB: J1.7, J5.3
unnamed: D1.2 (A), J5.2, JP2.2 (B)
unnamed: JP1.2 (B), JP3.1 (A), U2.6 (E2)
PHI2: J1.17, JP3.2 (B)
RB: J2.16 (~RD), U2.14 (~Y1)
RESB: J1.3, J2.12 (RESB)
RWB: J1.13, U2.1 (A0)
VCC: C1.1, C2.1, J1.2, J1.39, J2.1 (VCC), JP1.1 (A), U1.16 (VCC), U2.16 (VCC)
WB: J2.13 (~WR), U2.15 (~Y0)
~INT: D1.1 (K), J2.14 (IRQB), JP2.1 (A)

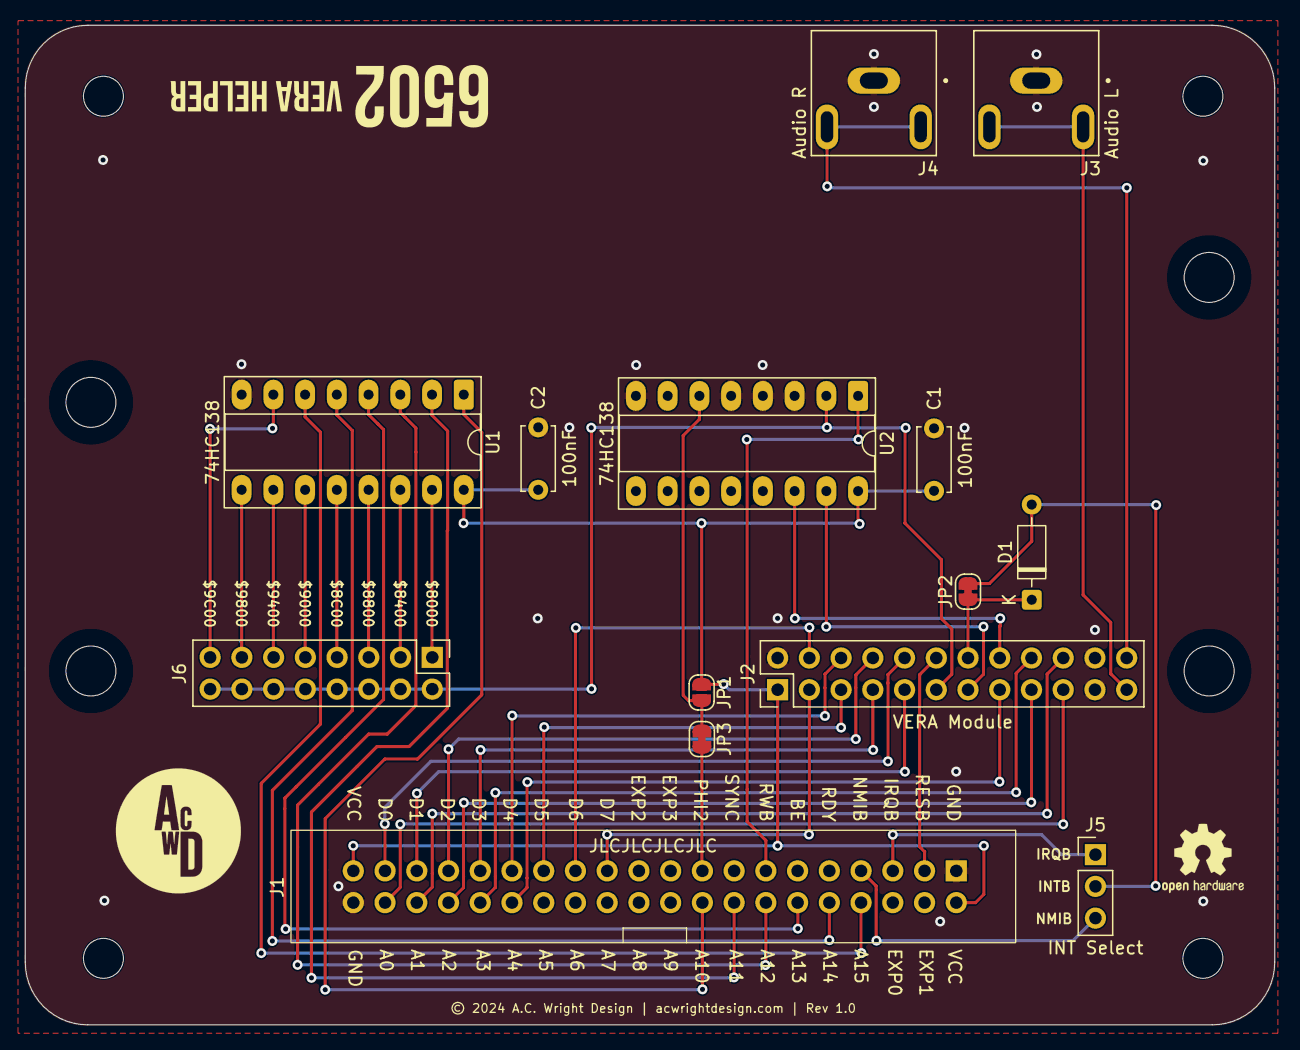
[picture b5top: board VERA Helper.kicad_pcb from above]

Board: 2 copper layers, 100.0 x 80.0 mm, 18 parts (0 on the bottom side), 42 nets.

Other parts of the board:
H1, H2, H3, H4: MountingHole; MountingHole_3.2mm_M3

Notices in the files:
Hardware/Serial Card/Rev 1.0/Serial Card.kicad_pcb:
© 2024 A.C. Wright Design | acwrightdesign.com | Rev 1.0
Hardware/VGA Card Pro/Rev 1.1/VGA Card Pro.kicad_pcb:
© 2024 A.C. Wright Design | acwrightdesign.com | Rev 1.1
